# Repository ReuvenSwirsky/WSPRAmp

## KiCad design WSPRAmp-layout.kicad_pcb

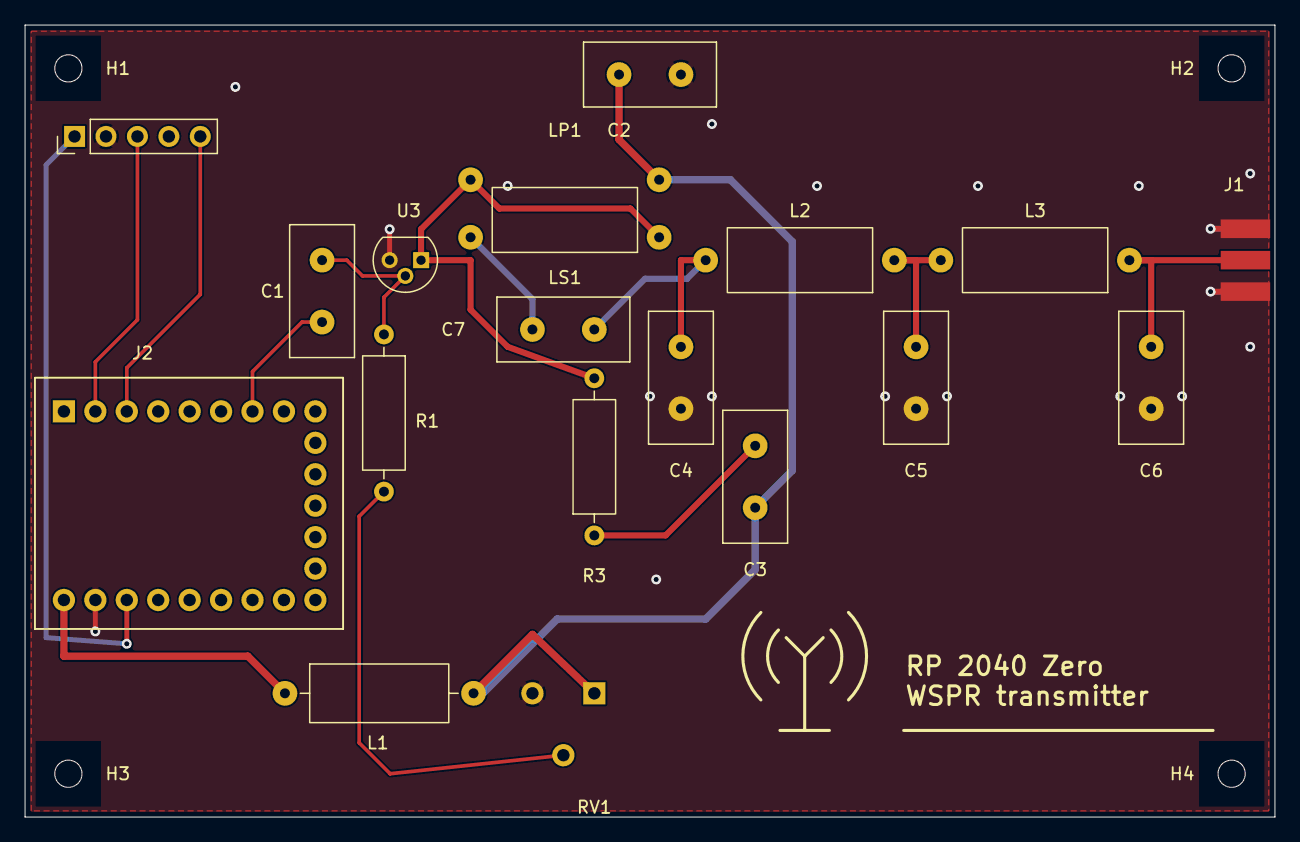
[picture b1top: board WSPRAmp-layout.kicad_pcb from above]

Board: 2 copper layers, 101.0 x 64.0 mm, 23 parts (0 on the bottom side), 15 nets.

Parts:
C1: 220pf; C_Disc_D10.5mm_W5.0mm_P5.00mm
C2: 10nf; C_Disc_D10.5mm_W5.0mm_P5.00mm
C3: 32pF; C_Disc_D10.5mm_W5.0mm_P5.00mm
C4, C6: 70.26pF; C_Disc_D10.5mm_W5.0mm_P5.00mm
C5: 227.36pF; C_Disc_D10.5mm_W5.0mm_P5.00mm
C7: 10nF; C_Disc_D10.5mm_W5.0mm_P5.00mm
H1, H2, H3, H4: MountingHole_2.2mm_M2
J1: Conn_Coaxial_Small; SMA_Edge_6.3mm
J2: Conn_01x05; PinHeader_1x05_P2.54mm_Vertical
L1: 1µH; L_Axial_L11.0mm_D4.5mm_P15.24mm_Horizontal_Fastron_MECC
L2, L3: .46µH; FT37-43_Upright_Inductor_P15.24mm
LP1: 2.5µH; FT37-43_Upright_Bifilar_Primary
LS1: 2.5µH; FT37-43_Upright_Bifilar_Secondary
R1: 100k; R_Axial_DIN0309_L9.0mm_D3.2mm_P12.70mm_Horizontal
R3: 100; R_Axial_DIN0309_L9.0mm_D3.2mm_P12.70mm_Horizontal
RV1: R_Potentiometer_US; Potentiometer_Trimmer_Horizontal_Triangle_P5.00mm_H5.00mm
RZ1: RP2040-Zero; RP2040-Zero_Headers_P2.54mm
U3: T2N7002AK_G0_00; TO-92

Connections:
+5V: L1.1, RZ1.23 (5V)
/PiGPIO4in: C1.1, RZ1.7 (GP6)
/out: C6.1, J1.1, L3.1
GND: C2.2, C4.2, C5.2, C6.2, J1.2, J2.2, RV1.3, RZ1.22 (GND), U3.3 (2)
unnamed: C2.1, C3.1, L1.2, LP1.1, RV1.1
unnamed: C3.2, R3.1
unnamed: C4.1, C7.2, L2.2
unnamed: C5.1, L2.1, L3.2
unnamed: C7.1, LS1.2
unnamed: J2.1, RZ1.21 (3V3)
unnamed: J2.3, RZ1.2 (GP1)
unnamed: J2.5, RZ1.3 (GP2)
unnamed: R1.2, RV1.2
unnamed: C1.2, R1.1, U3.2 (1)
unnamed: LP1.2, LS1.1, R3.2, U3.1 (3)
